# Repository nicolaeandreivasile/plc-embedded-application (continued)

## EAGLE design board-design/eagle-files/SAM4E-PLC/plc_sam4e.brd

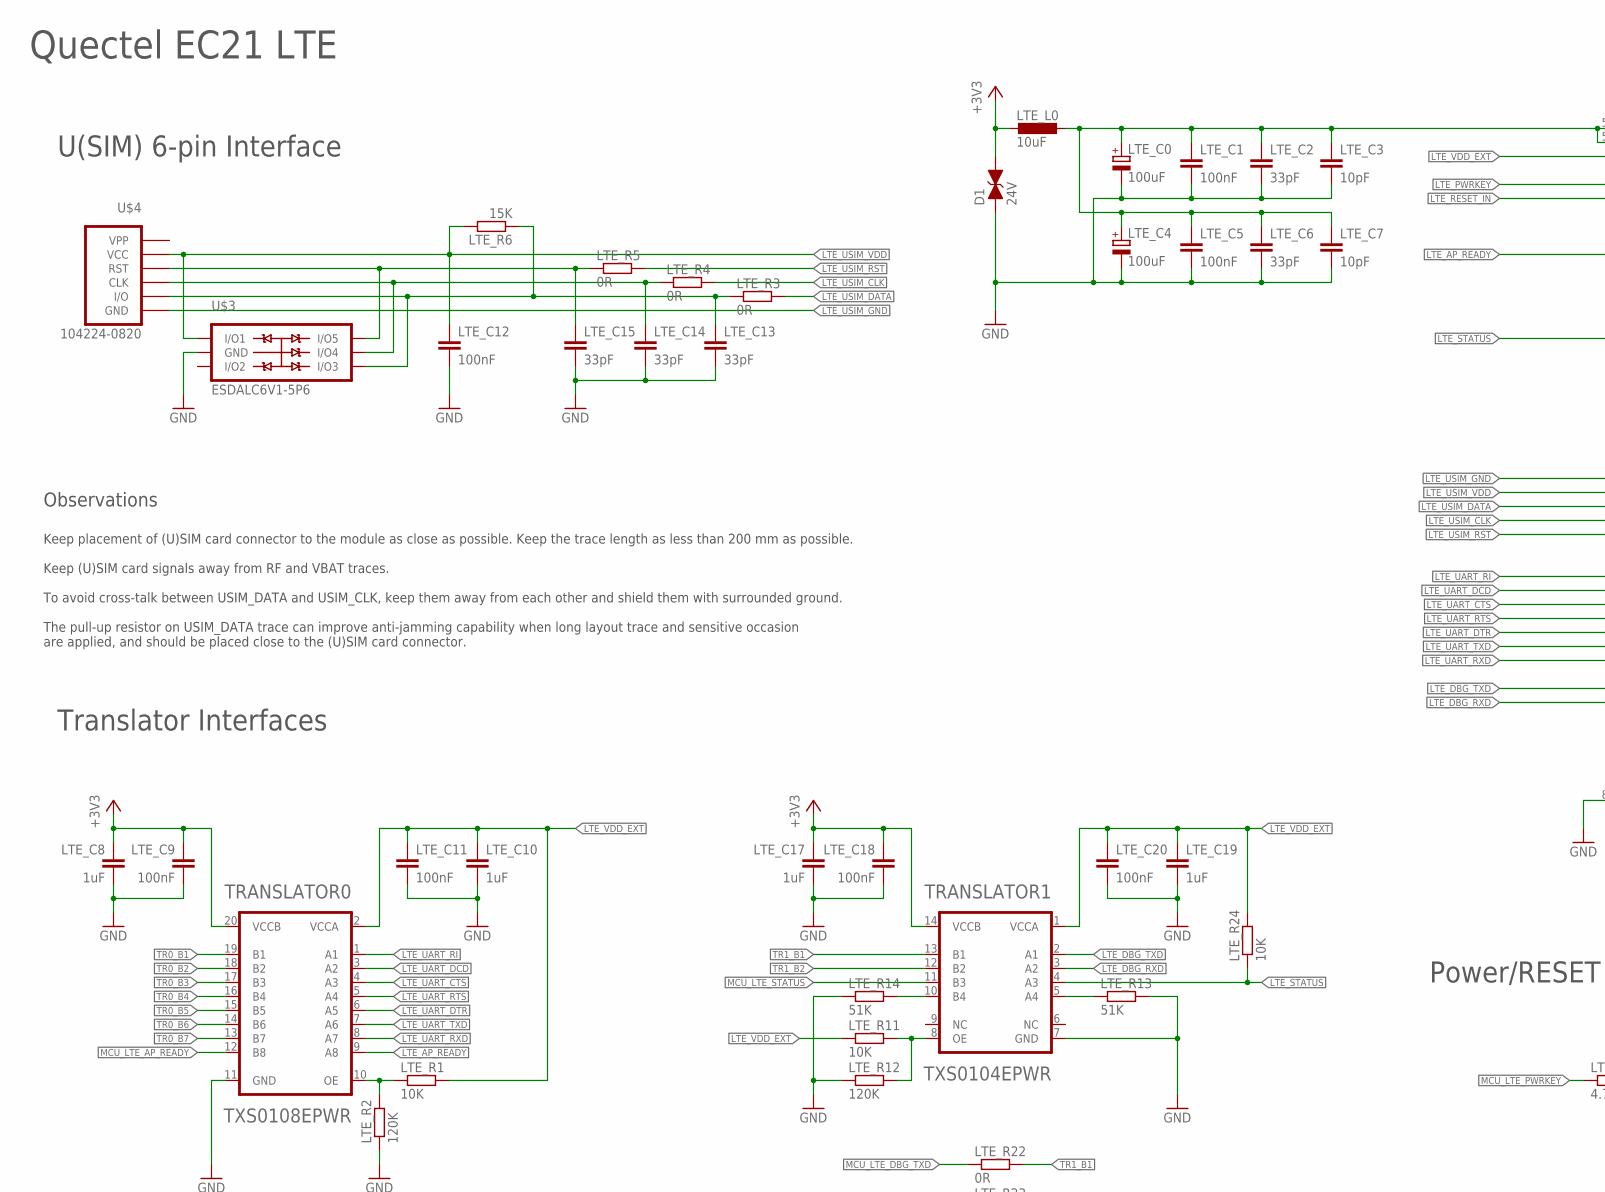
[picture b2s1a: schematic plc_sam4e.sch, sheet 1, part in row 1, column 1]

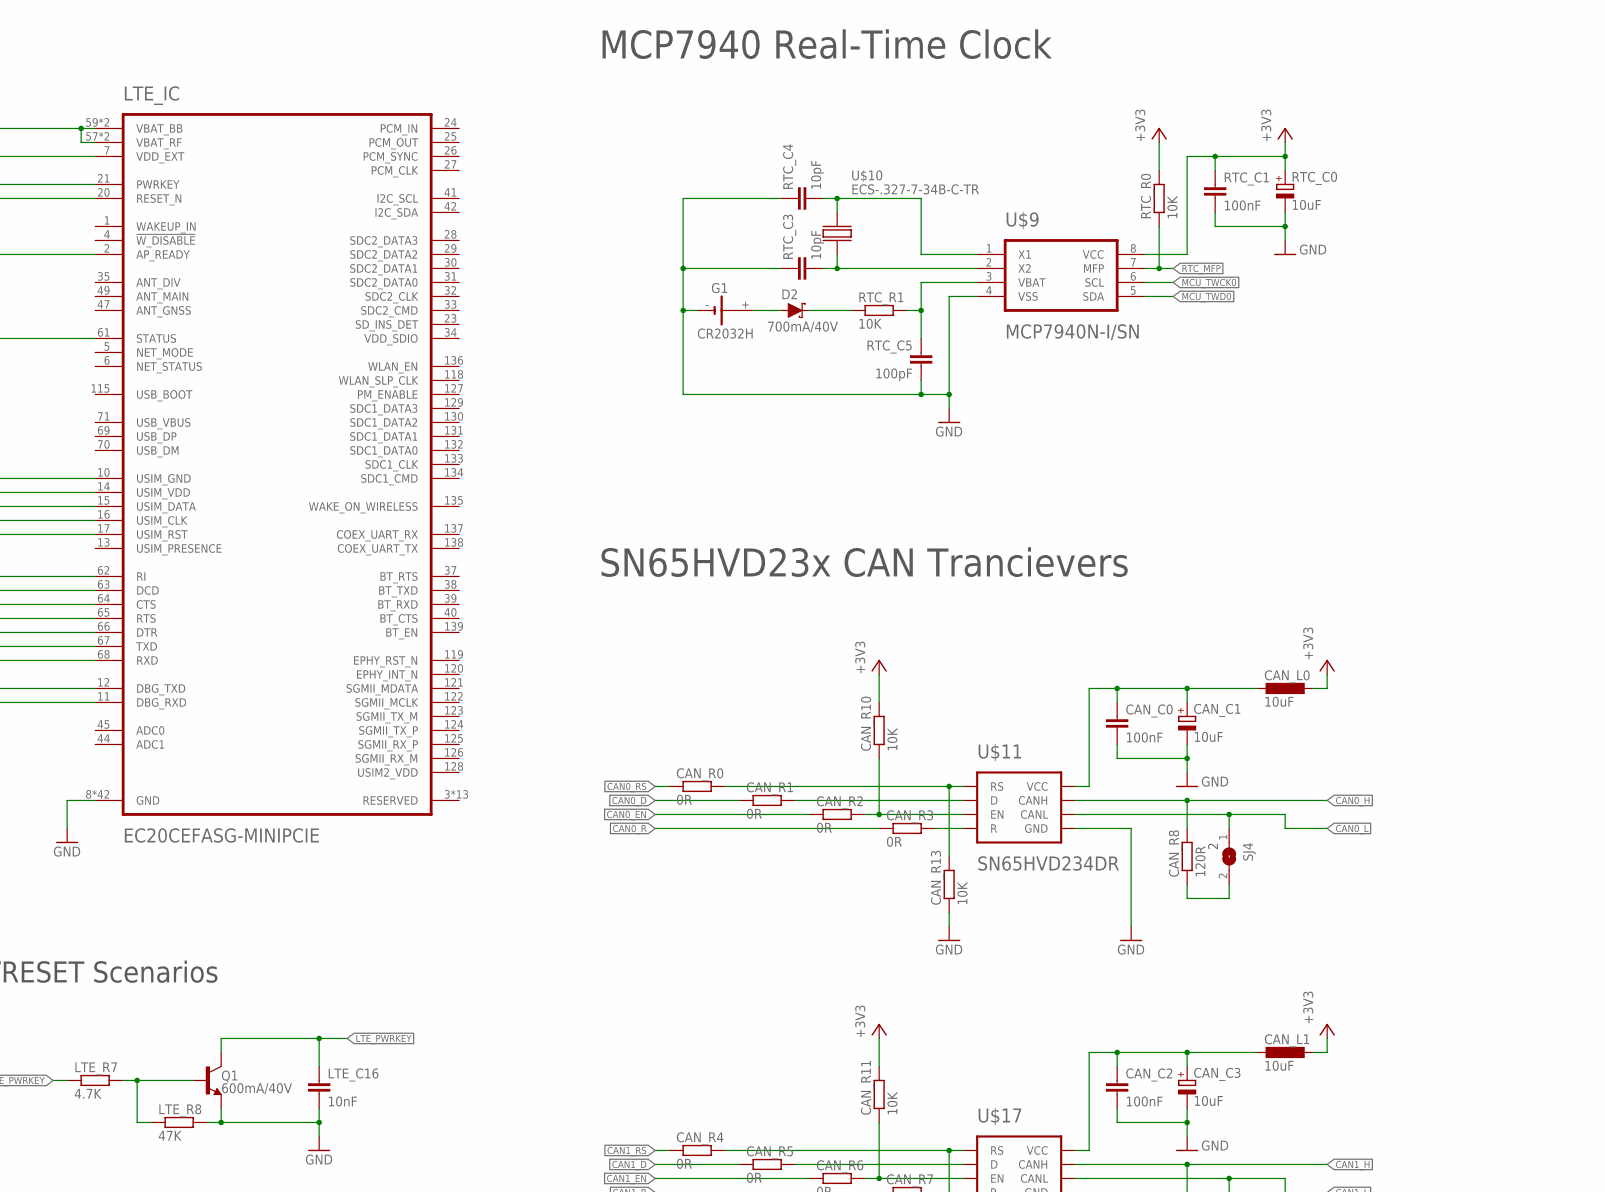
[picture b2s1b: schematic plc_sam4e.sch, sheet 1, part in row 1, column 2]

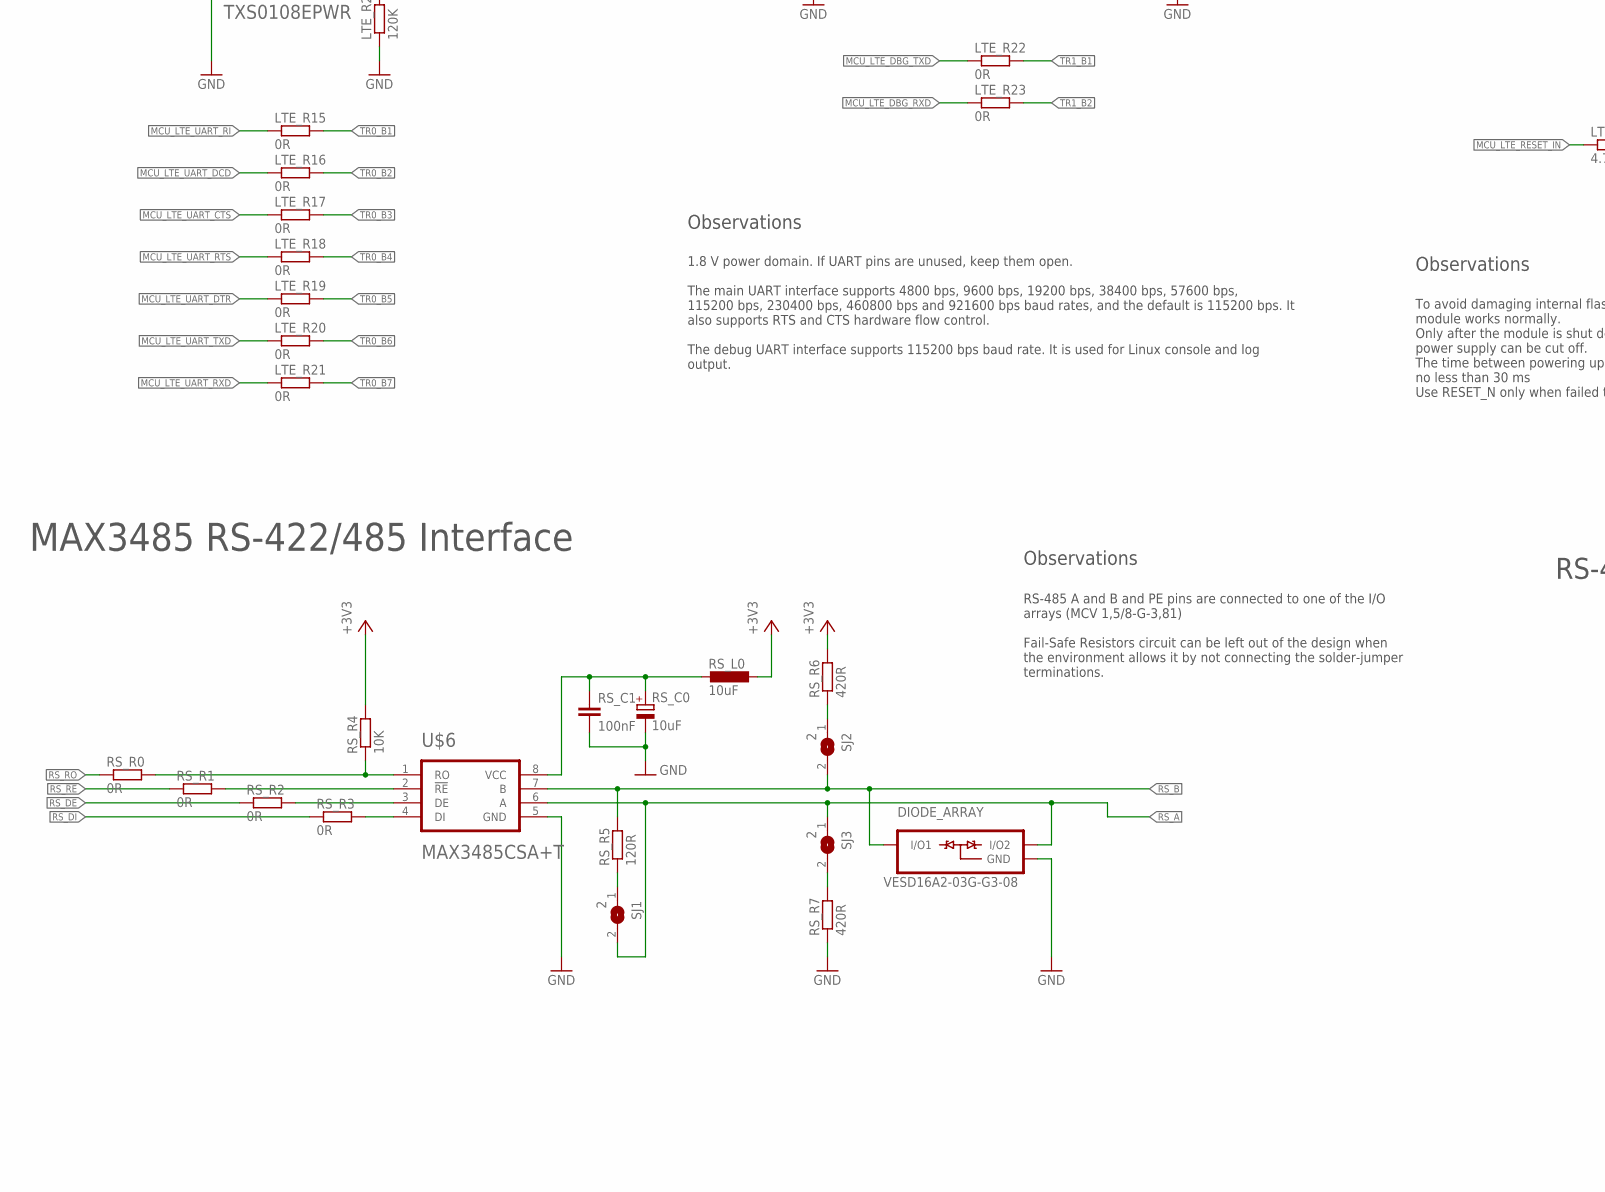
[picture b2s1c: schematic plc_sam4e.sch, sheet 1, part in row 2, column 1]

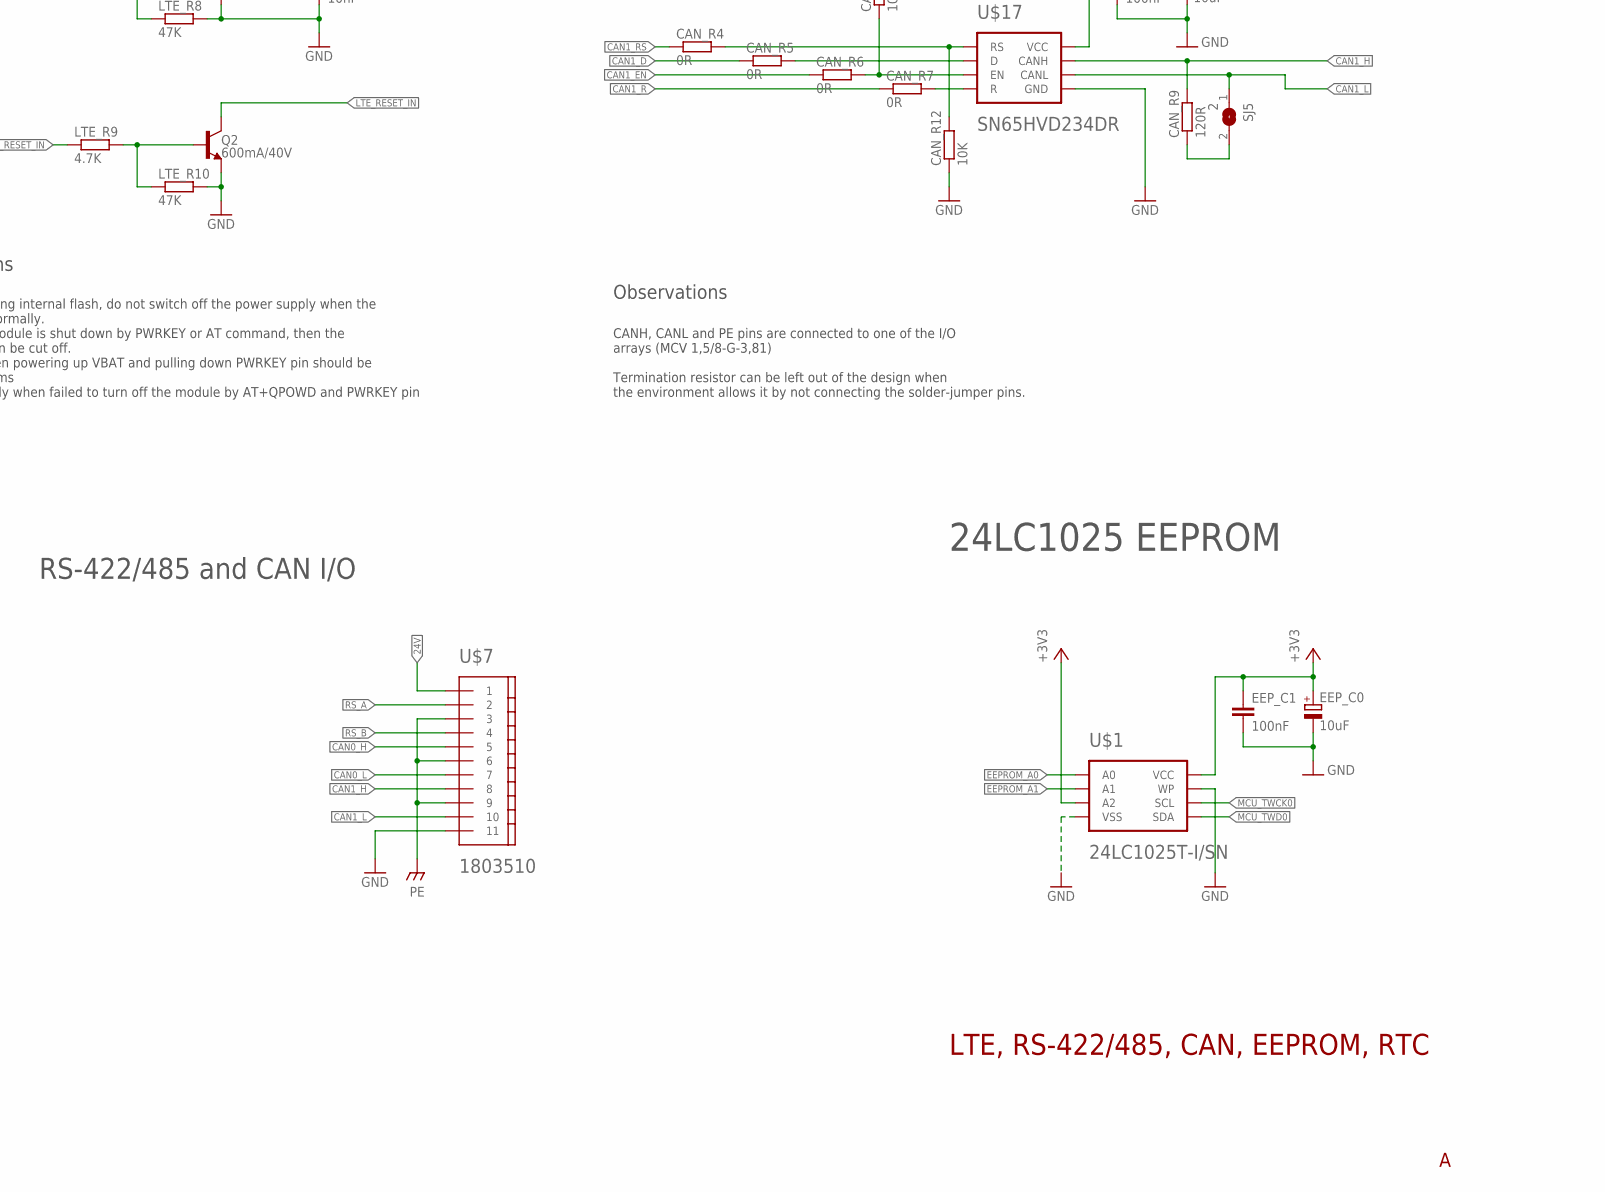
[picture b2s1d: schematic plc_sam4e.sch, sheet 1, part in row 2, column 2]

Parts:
CAN_C0, CAN_C2: 100nF; C0402
CAN_C1, CAN_C3: 10uF; SMC_B
CAN_L0, CAN_L1: 10uF; L1812
CAN_R0, CAN_R1, CAN_R2, CAN_R3, CAN_R4, CAN_R5, CAN_R6, CAN_R7: 0R; R0402
CAN_R8, CAN_R9: 120R; R0402
CAN_R10, CAN_R11, CAN_R12, CAN_R13: 10K; R0402
D1: 24V; 0603
D2: 700mA/40V; SOT23-3
DIODE_ARRAY: VESD16A2-03G-G3-08; SOT-323-3
EEP_C0: 10uF; SMC_B
EEP_C1: 100nF; C0402
G1: CR2032H
LTE_C0, LTE_C4: 100uF; SMC_B
LTE_C1, LTE_C5, LTE_C9, LTE_C11, LTE_C12, LTE_C18, LTE_C20: 100nF; C0402
LTE_C2, LTE_C6, LTE_C13, LTE_C14, LTE_C15: 33pF; C0402
LTE_C3, LTE_C7: 10pF; C0402
LTE_C8, LTE_C10, LTE_C17, LTE_C19: 1uF; C0402
LTE_C16: 10nF; C0402
LTE_IC: EC20CEFASG-MINIPCIE; EC21
LTE_L0: 10uF; L1812
LTE_R1, LTE_R11, LTE_R24: 10K; R0402
LTE_R2, LTE_R12: 120K; R0402
LTE_R3, LTE_R4, LTE_R5, LTE_R15, LTE_R16, LTE_R17, LTE_R18, LTE_R19, LTE_R20, LTE_R21, LTE_R22, LTE_R23: 0R; R0402
LTE_R6: 15K; R0402
LTE_R7, LTE_R9: 4.7K; R0402
LTE_R8, LTE_R10: 47K; R0402
LTE_R13, LTE_R14: 51K; R0402
Q1, Q2: 600mA/40V; SOT23-3
RS_C0: 10uF; SMC_B
RS_C1: 100nF; C0402
RS_L0: 10uF; L1812
RS_R0, RS_R1, RS_R2, RS_R3: 0R; R0402
RS_R4: 10K; R0402
RS_R5: 120R; R0402
RS_R6, RS_R7: 420R; R0402
RTC_C0: 10uF; SMC_B
RTC_C1: 100nF; C0402
RTC_C3, RTC_C4: 10pF; C0402
RTC_C5: 100pF; C0402
RTC_R0, RTC_R1: 10K; R0402
SJ1, SJ2, SJ3, SJ4, SJ5: 2; SJ
TRANSLATOR0: TXS0108EPWR; TSSOP-20
TRANSLATOR1: TXS0104EPWR; TSSOP-14
U$1: 24LC1025T-I/SN; SOIC-8
U$3: ESDALC6V1-5P6; SOT-666
U$4: 104224-0820
U$6: MAX3485CSA+T; SOIC-8
U$7: 1803510
U$9: MCP7940N-I/SN; SOIC-8
U$10: ECS-.327-7-34B-C-TR; 3.2X1.5MM
U$11, U$17: SN65HVD234DR; SOIC-8

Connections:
24V: U$7.1; also elsewhere on the board
+3V3: CAN_L0.1, CAN_L1.1, CAN_R10.2, CAN_R11.2, D1.2 (C), EEP_C0.+, EEP_C1.1, LTE_C8.1, LTE_C9.1, LTE_C17.1, LTE_C18.1, LTE_L0.2, RS_L0.1, RS_R4.2, RS_R6.2, RTC_C0.+, RTC_C1.1, RTC_R0.2, TRANSLATOR0.20 (VCCB), TRANSLATOR1.14 (VCCB), U$1.3 (A2), U$1.8 (VCC), U$9.8 (VCC); also elsewhere on the board
CAN0_D: CAN_R1.1; also elsewhere on the board
CAN0_EN: CAN_R2.1; also elsewhere on the board
CAN0_H: CAN_R8.2, U$7.5, U$11.7 (CANH)
CAN0_L: SJ4.1, U$7.7, U$11.6 (CANL)
CAN0_R: CAN_R3.1; also elsewhere on the board
CAN0_RS: CAN_R0.1; also elsewhere on the board
CAN1_D: CAN_R5.1; also elsewhere on the board
CAN1_EN: CAN_R6.1; also elsewhere on the board
CAN1_H: CAN_R9.2, U$7.8, U$17.7 (CANH)
CAN1_L: SJ5.1, U$7.10, U$17.6 (CANL)
CAN1_R: CAN_R7.1; also elsewhere on the board
CAN1_RS: CAN_R4.1; also elsewhere on the board
EEPROM_A0: U$1.1 (A0); also elsewhere on the board
EEPROM_A1: U$1.2 (A1); also elsewhere on the board
GND: CAN_C0.2, CAN_C1.-, CAN_C2.2, CAN_C3.-, CAN_R12.1, CAN_R13.1, D1.1 (A), DIODE_ARRAY.3 (GND), EEP_C0.-, EEP_C1.2, G1.-, LTE_C0.-, LTE_C1.2, LTE_C2.2, LTE_C3.2, LTE_C4.-, LTE_C5.2, LTE_C6.2, LTE_C7.2, LTE_C8.2, LTE_C9.2, LTE_C10.2, LTE_C11.2, LTE_C12.2, LTE_C13.2, LTE_C14.2, LTE_C15.2, LTE_C16.2, LTE_C17.2, LTE_C18.2, LTE_C19.2, LTE_C20.2, LTE_IC.8 (GND), LTE_IC.9 (GND), LTE_IC.19 (GND), LTE_IC.22 (GND), LTE_IC.36 (GND), LTE_IC.46 (GND), LTE_IC.48 (GND), LTE_IC.50 (GND), LTE_IC.51 (GND), LTE_IC.52 (GND), LTE_IC.53 (GND), LTE_IC.54 (GND), LTE_IC.56 (GND), LTE_IC.72 (GND), LTE_IC.85 (GND), LTE_IC.86 (GND), LTE_IC.87 (GND), LTE_IC.88 (GND), LTE_IC.89 (GND), LTE_IC.90 (GND), LTE_IC.91 (GND), LTE_IC.92 (GND), LTE_IC.93 (GND), LTE_IC.94 (GND), LTE_IC.95 (GND), LTE_IC.96 (GND), LTE_IC.97 (GND), LTE_IC.98 (GND), LTE_IC.99 (GND), LTE_IC.100 (GND), LTE_IC.101 (GND), LTE_IC.102 (GND), LTE_IC.103 (GND), LTE_IC.104 (GND), LTE_IC.105 (GND), LTE_IC.106 (GND), LTE_IC.107 (GND), LTE_IC.108 (GND), LTE_IC.109 (GND), LTE_IC.110 (GND), LTE_IC.111 (GND), LTE_IC.112 (GND), LTE_R2.1, LTE_R8.2, LTE_R10.2, LTE_R12.1, LTE_R13.2, LTE_R14.1, Q1.2 (E), Q2.2 (E), RS_C0.-, RS_C1.2, RS_R7.1, RTC_C0.-, RTC_C1.2, RTC_C3.1, RTC_C4.1, RTC_C5.2, TRANSLATOR0.11 (GND), TRANSLATOR1.7 (GND), U$1.4 (VSS), U$1.7 (WP), U$3.2 (GND), U$6.5 (GND), U$7.11, U$9.4 (VSS), U$11.2 (GND), U$17.2 (GND); also elsewhere on the board
LTE_AP_READY: LTE_IC.2 (AP_READY), TRANSLATOR0.9 (A8)
LTE_DBG_RXD: LTE_IC.11 (DBG_RXD), TRANSLATOR1.3 (A2)
LTE_DBG_TXD: LTE_IC.12 (DBG_TXD), TRANSLATOR1.2 (A1)
LTE_PWRKEY: LTE_C16.1, LTE_IC.21 (PWRKEY), Q1.3 (C)
LTE_RESET_IN: LTE_IC.20 (RESET_N), Q2.3 (C)
LTE_STATUS: LTE_IC.61 (STATUS), LTE_R24.1, TRANSLATOR1.4 (A3)
LTE_UART_CTS: LTE_IC.64 (CTS), TRANSLATOR0.4 (A3)
LTE_UART_DCD: LTE_IC.63 (DCD), TRANSLATOR0.3 (A2)
LTE_UART_DTR: LTE_IC.66 (DTR), TRANSLATOR0.6 (A5)
LTE_UART_RI: LTE_IC.62 (RI), TRANSLATOR0.1 (A1)
LTE_UART_RTS: LTE_IC.65 (RTS), TRANSLATOR0.5 (A4)
LTE_UART_RXD: LTE_IC.68 (RXD), TRANSLATOR0.8 (A7)
LTE_UART_TXD: LTE_IC.67 (TXD), TRANSLATOR0.7 (A6)
LTE_USIM_CLK: LTE_IC.16 (USIM_CLK), LTE_R4.2
LTE_USIM_DATA: LTE_IC.15 (USIM_DATA), LTE_R3.2
LTE_USIM_GND: LTE_IC.10 (USIM_GND), U$4.G1 (GND), U$4.G2 (GND), U$4.G3 (GND), U$4.G4 (GND), U$4.S4 (GND)
LTE_USIM_RST: LTE_IC.17 (USIM_RST), LTE_R5.2
LTE_USIM_VDD: LTE_C12.1, LTE_IC.14 (USIM_VDD), LTE_R6.2, U$3.1 (I/O1), U$4.S1 (VCC)
LTE_VBAT: LTE_C0.+, LTE_C1.1, LTE_C2.1, LTE_C3.1, LTE_C4.+, LTE_C5.1, LTE_C6.1, LTE_C7.1, LTE_IC.57 (VBAT_RF), LTE_IC.58 (VBAT_RF), LTE_IC.59 (VBAT_BB), LTE_IC.60 (VBAT_BB), LTE_L0.1
LTE_VDD_EXT: LTE_C10.1, LTE_C11.1, LTE_C19.1, LTE_C20.1, LTE_IC.7 (VDD_EXT), LTE_R1.2, LTE_R11.1, LTE_R24.2, TRANSLATOR0.2 (VCCA), TRANSLATOR1.1 (VCCA)
MCU_LTE_AP_READY: TRANSLATOR0.12 (B8); also elsewhere on the board
MCU_LTE_DBG_RXD: LTE_R23.1; also elsewhere on the board
MCU_LTE_DBG_TXD: LTE_R22.1; also elsewhere on the board
MCU_LTE_PWRKEY: LTE_R7.1; also elsewhere on the board
MCU_LTE_RESET_IN: LTE_R9.1; also elsewhere on the board
MCU_LTE_STATUS: TRANSLATOR1.11 (B3); also elsewhere on the board
MCU_LTE_UART_CTS: LTE_R17.1; also elsewhere on the board
MCU_LTE_UART_DCD: LTE_R16.1; also elsewhere on the board
MCU_LTE_UART_DTR: LTE_R19.1; also elsewhere on the board
MCU_LTE_UART_RI: LTE_R15.1; also elsewhere on the board
MCU_LTE_UART_RTS: LTE_R18.1; also elsewhere on the board
MCU_LTE_UART_RXD: LTE_R21.1; also elsewhere on the board
MCU_LTE_UART_TXD: LTE_R20.1; also elsewhere on the board
MCU_TWCK0: U$1.6 (SCL), U$9.6 (SCL); also elsewhere on the board
MCU_TWD0: U$1.5 (SDA), U$9.5 (SDA); also elsewhere on the board
unnamed: LTE_R7.2, LTE_R8.1, Q1.1 (B)
unnamed: RS_R0.2, RS_R4.1, U$6.1 (RO)
unnamed: RS_R1.2, U$6.2 (!RE)
unnamed: RS_R2.2, U$6.3 (DE)
unnamed: LTE_R9.2, LTE_R10.1, Q2.1 (B)
unnamed: LTE_R14.2, TRANSLATOR1.10 (B4)
unnamed: RTC_C4.2, U$9.1 (X1), U$10.2
unnamed: RS_R3.2, U$6.4 (DI)
unnamed: CAN_R3.2, U$11.4 (R)
unnamed: RTC_C3.2, U$9.2 (X2), U$10.1
unnamed: CAN_R2.2, CAN_R10.1, U$11.5 (EN)
unnamed: D2.3 (C), RTC_R1.1
unnamed: D2.1 (A), G1.+
unnamed: LTE_R13.1, TRANSLATOR1.5 (A4)
unnamed: RTC_C5.1, RTC_R1.2, U$9.3 (VBAT)
unnamed: CAN_R1.2, U$11.1 (D)
unnamed: RS_R5.1, SJ1.1
unnamed: CAN_R0.2, CAN_R13.2, U$11.8 (RS)
unnamed: RS_R6.1, SJ2.1
unnamed: RS_R7.2, SJ3.2
unnamed: LTE_R1.1, LTE_R2.2, TRANSLATOR0.10 (OE)
unnamed: CAN_R4.2, CAN_R12.2, U$17.8 (RS)
unnamed: CAN_R5.2, U$17.1 (D)
unnamed: CAN_R6.2, CAN_R11.1, U$17.5 (EN)
unnamed: CAN_R7.2, U$17.4 (R)
unnamed: RS_C0.+, RS_C1.1, RS_L0.2, U$6.8 (VCC)
unnamed: CAN_R8.1, SJ4.2
unnamed: CAN_R9.1, SJ5.2
unnamed: LTE_C15.1, LTE_R5.1, U$3.6 (I/O5), U$4.S2 (RST)
unnamed: LTE_C14.1, LTE_R4.1, U$3.5 (I/O4), U$4.S3 (CLK)
unnamed: LTE_C13.1, LTE_R3.1, LTE_R6.1, U$3.4 (I/O3), U$4.S6 (I/O)
unnamed: CAN_C0.1, CAN_C1.+, CAN_L0.2, U$11.3 (VCC)
unnamed: CAN_C2.1, CAN_C3.+, CAN_L1.2, U$17.3 (VCC)
unnamed: LTE_R11.2, LTE_R12.2, TRANSLATOR1.8 (OE)
P$1: U$7.3, U$7.6, U$7.9; also elsewhere on the board
RS_!RE: RS_R1.1; also elsewhere on the board
RS_A: DIODE_ARRAY.2 (I/O2), SJ1.2, SJ3.1, U$6.6 (A), U$7.2
RS_B: DIODE_ARRAY.1 (I/O1), RS_R5.2, SJ2.2, U$6.7 (B), U$7.4
RS_DE: RS_R2.1; also elsewhere on the board
RS_DI: RS_R3.1; also elsewhere on the board
RS_RO: RS_R0.1; also elsewhere on the board
RTC_MFP: RTC_R0.1, U$9.7 (MFP); also elsewhere on the board
TR0_B1: LTE_R15.2, TRANSLATOR0.19 (B1)
TR0_B2: LTE_R16.2, TRANSLATOR0.18 (B2)
TR0_B3: LTE_R17.2, TRANSLATOR0.17 (B3)
TR0_B4: LTE_R18.2, TRANSLATOR0.16 (B4)
TR0_B5: LTE_R19.2, TRANSLATOR0.15 (B5)
TR0_B6: LTE_R20.2, TRANSLATOR0.14 (B6)
TR0_B7: LTE_R21.2, TRANSLATOR0.13 (B7)
TR1_B1: LTE_R22.2, TRANSLATOR1.13 (B1)
TR1_B2: LTE_R23.2, TRANSLATOR1.12 (B2)

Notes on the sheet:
U(SIM) 6-pin Interface
Translator Interfaces
Power/RESET Scenarios
Observations
Quectel EC21 LTE
1.8 V power domain. If UART pins are unused, keep them open. The main UART interface supports 4800 bps, 9600 bps, 19200 bps, 38400 bps, 57600 bps, 115200 bps, 230400 bps, 460800 bps and 921600 bps baud rates, and the default is 115200 bps. It also supports RTS and CTS hardware flow control. The deb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
Keep placement of (U)SIM card connector to the module as close as possible. Keep the trace length as less than 200 mm as possible. Keep (U)SIM card signals away from RF and VBAT traces. To avoid cross-talk between USIM_DATA and USIM_CLK, keep them away from each other and shield them with surrounde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
To avoid damaging internal flash, do not switch off the power supply when the module works normally. Only after the module is shut down by PWRKEY or AT command, then the power supply can be cut off. The time between powering up VBAT and pulling down PWRKEY pin should be no less than 30 ms Use RESET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
MAX3485 RS-422/485 Interface
RS-485 A and B and PE pins are connected to one of the I/O arrays (MCV 1,5/8-G-3,81) Fail-Safe Resistors circuit can be left out of the design when the environment allows it by not connecting the solder-jumper terminations.
MCP7940 Real-Time Clock
SN65HVD23x CAN Trancievers
CANH, CANL and PE pins are connected to one of the I/O arrays (MCV 1,5/8-G-3,81) Termination resistor can be left out of the design when the environment allows it by not connecting the solder-jumper pins.
RS-422/485 and CAN I/O
24LC1025 EEPROM
LTE, RS-422/485, CAN, EEPROM, RTC
